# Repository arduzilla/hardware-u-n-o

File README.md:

# hardware-u-n-o

Arduino Uno format board

- Microconroller: STM32H750VB 
  - 416MHz Clock (Max 480)
  - Code & Data cache
  - 1MB SRAM
  - 128KB Flash + 2MB QSPI (direct execution from the QSPI)
  - plenty of peripherals
- RS485
- 6x Servo connector
- ... and much more

how to edit the schematics and the board layout:

install Eagle (free software for non commercial use)  https://www.autodesk.co.uk/products/eagle/free-download

clone (or fork) the arduzilla repo:
```
git clone https://github.com/arduzilla/hardware-u-n-o.git
```

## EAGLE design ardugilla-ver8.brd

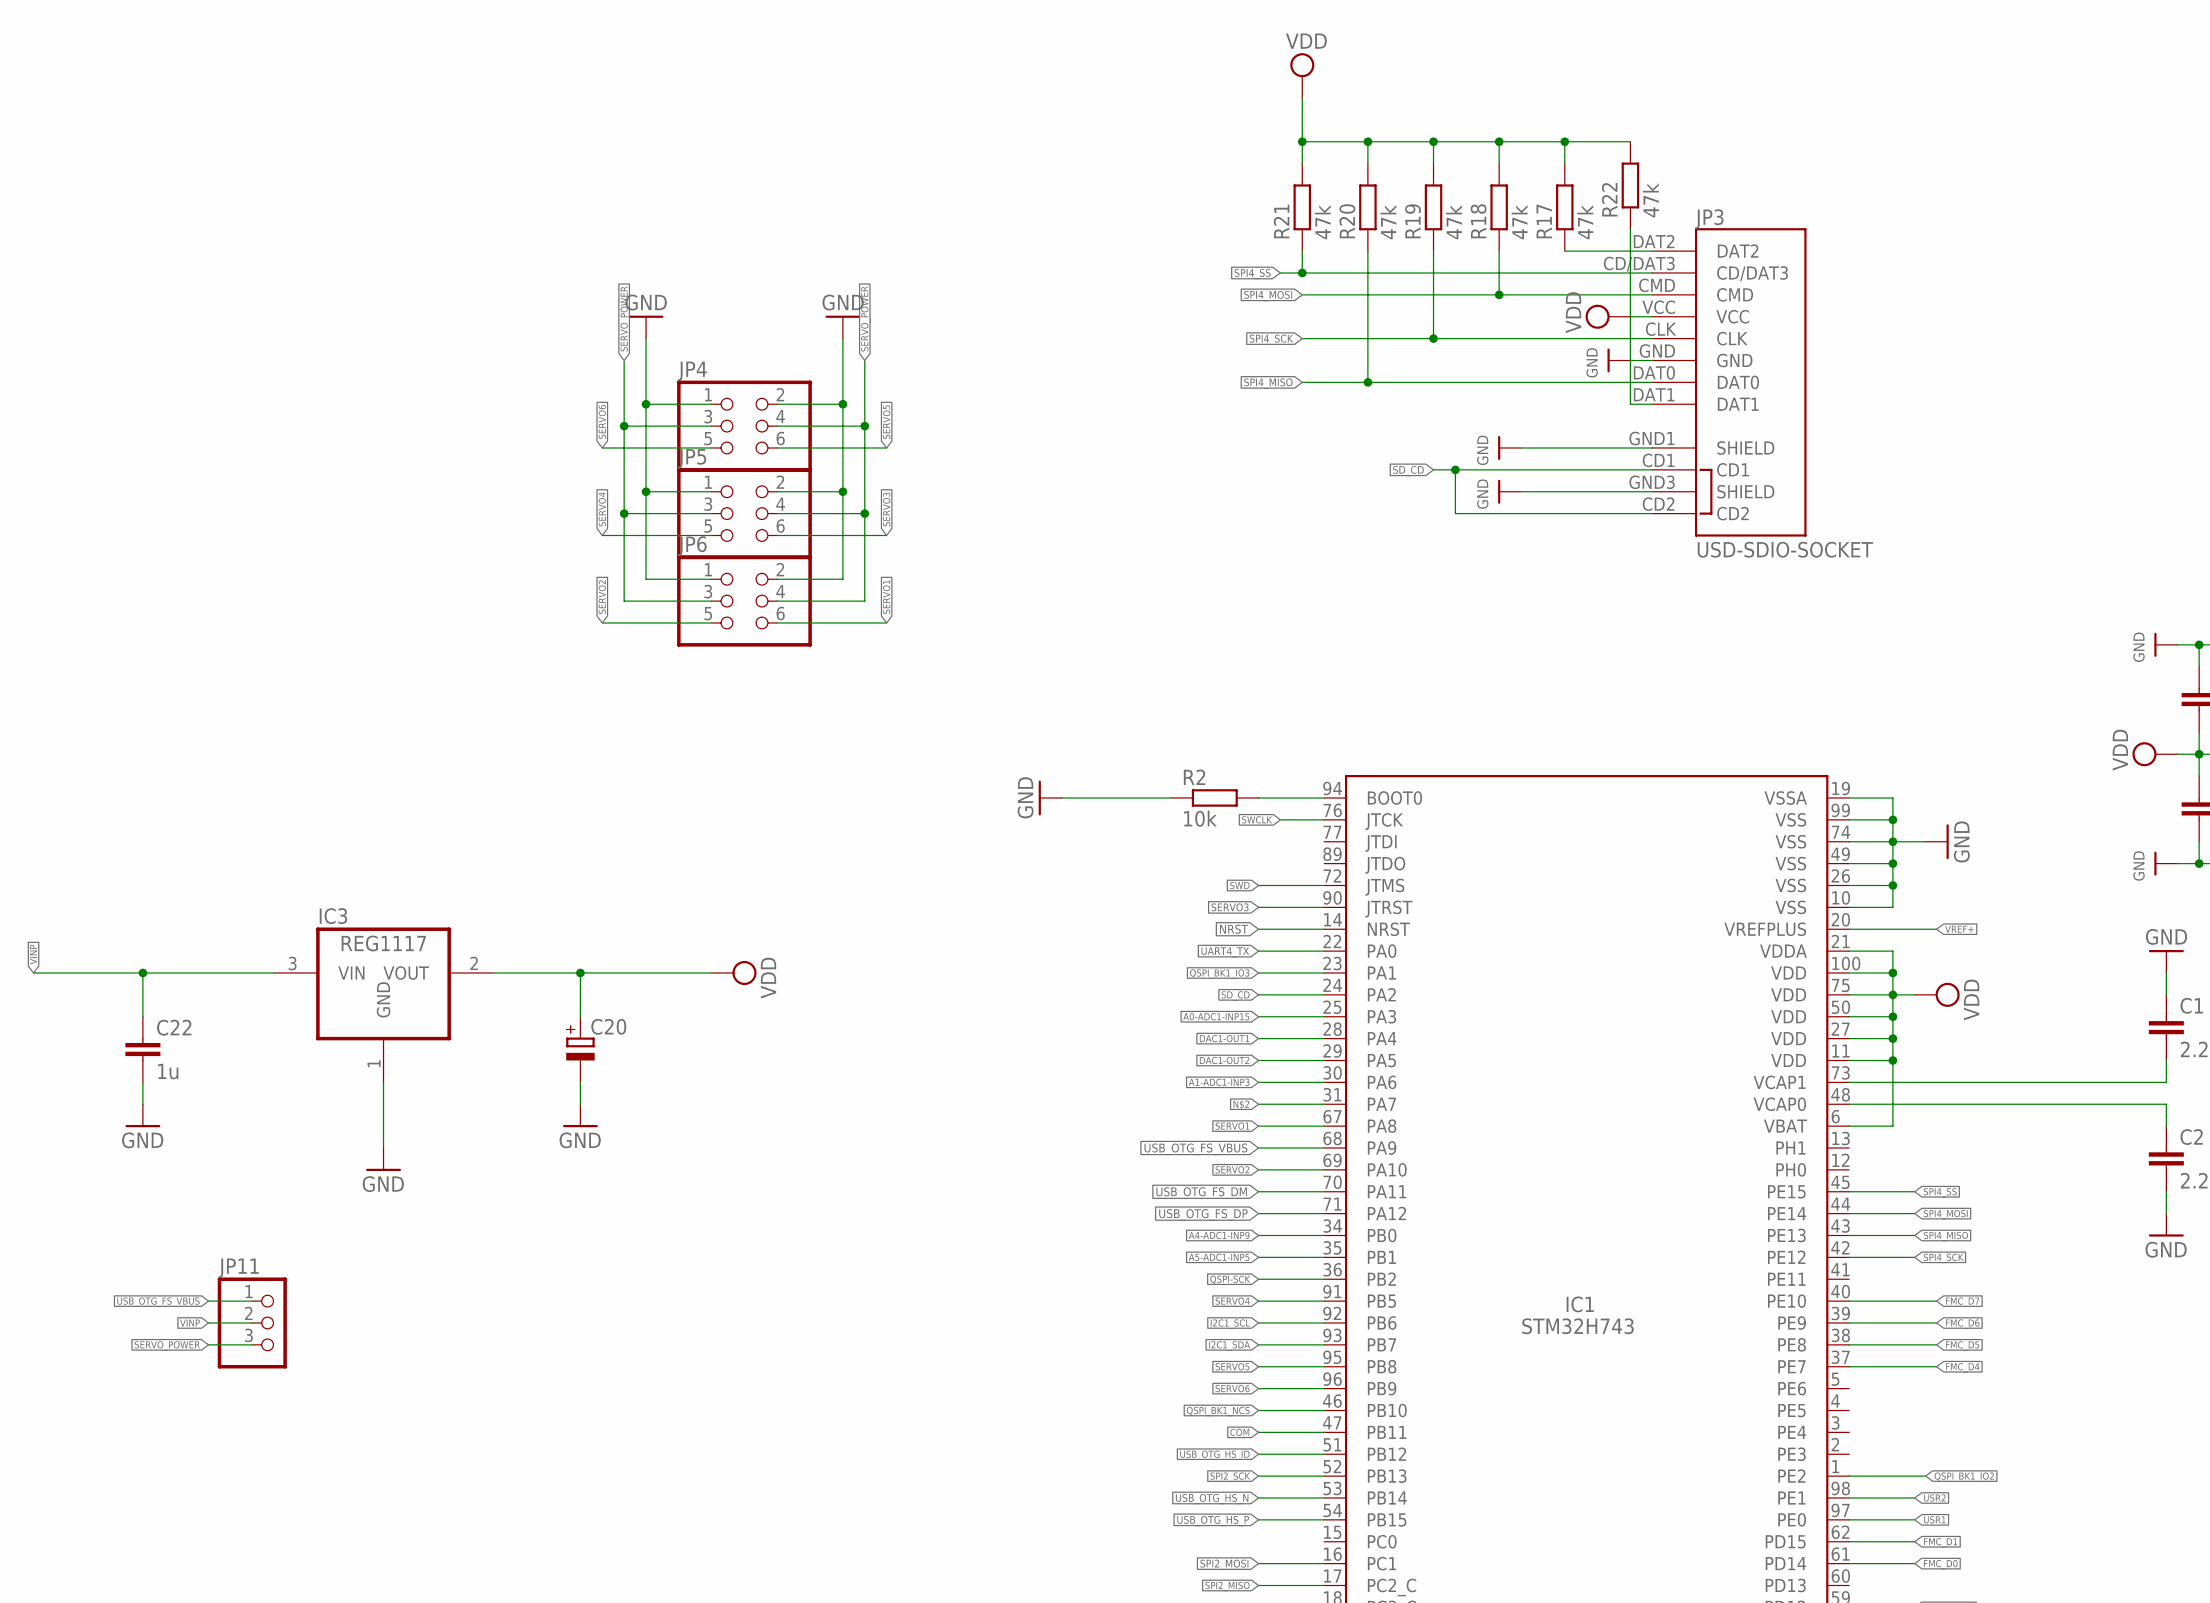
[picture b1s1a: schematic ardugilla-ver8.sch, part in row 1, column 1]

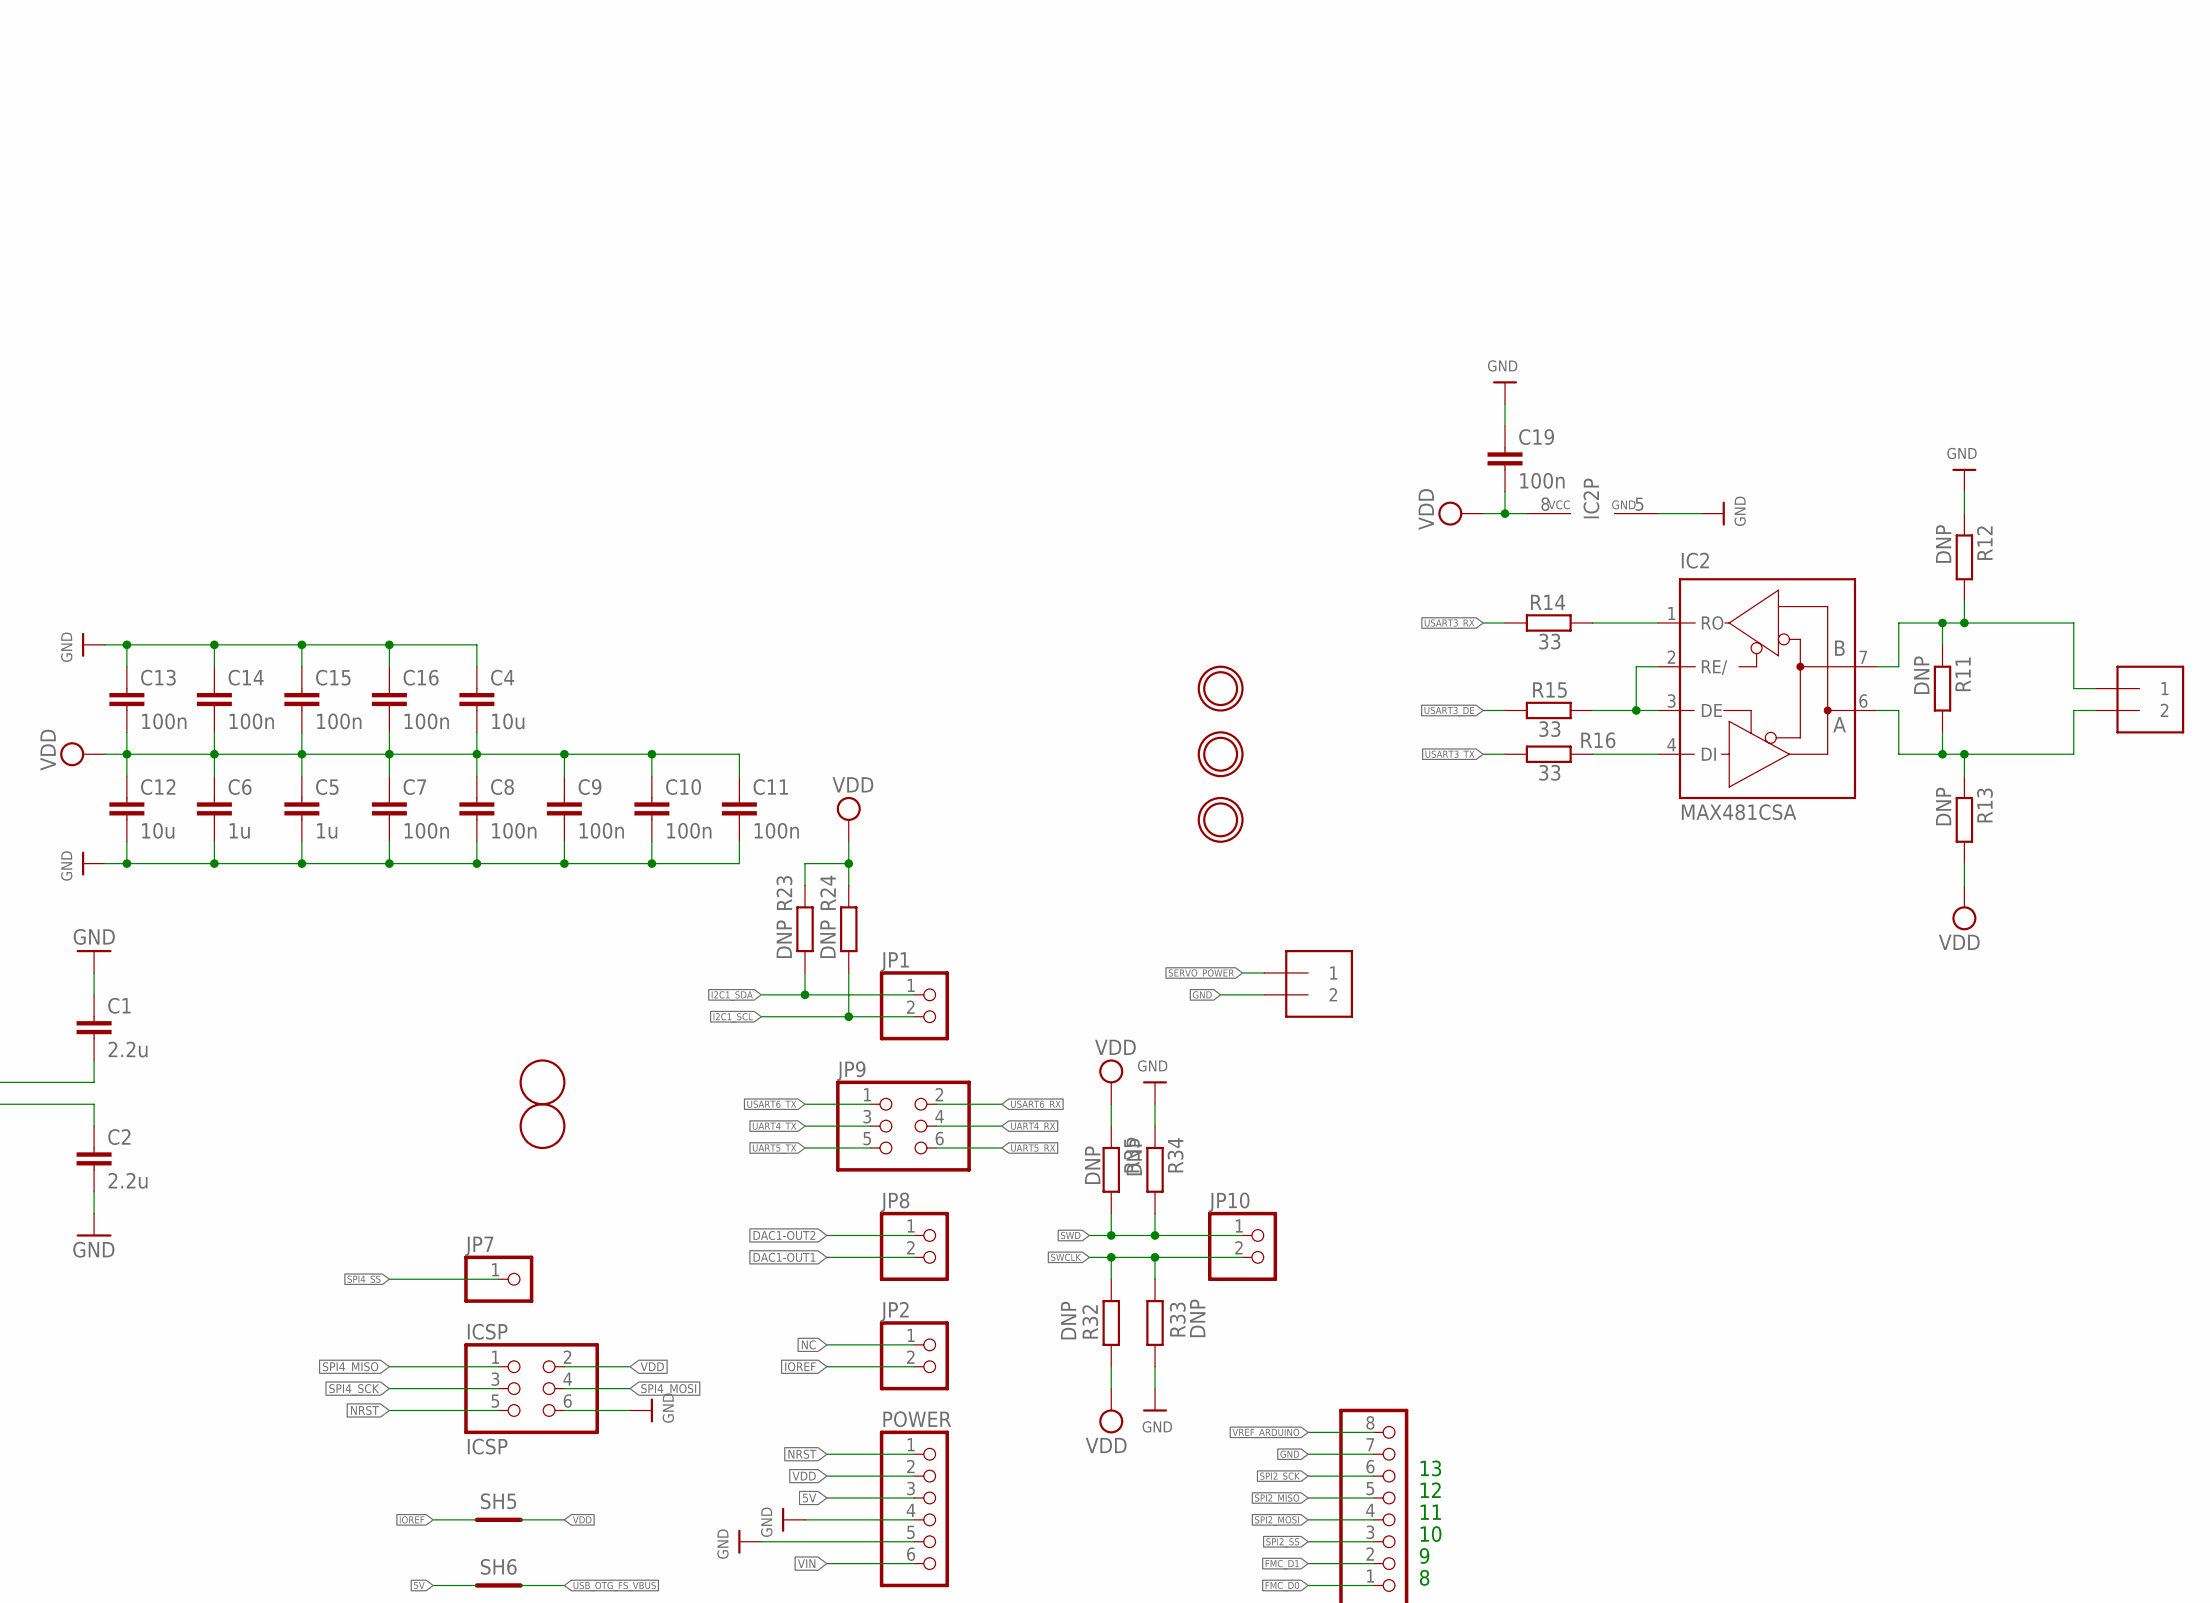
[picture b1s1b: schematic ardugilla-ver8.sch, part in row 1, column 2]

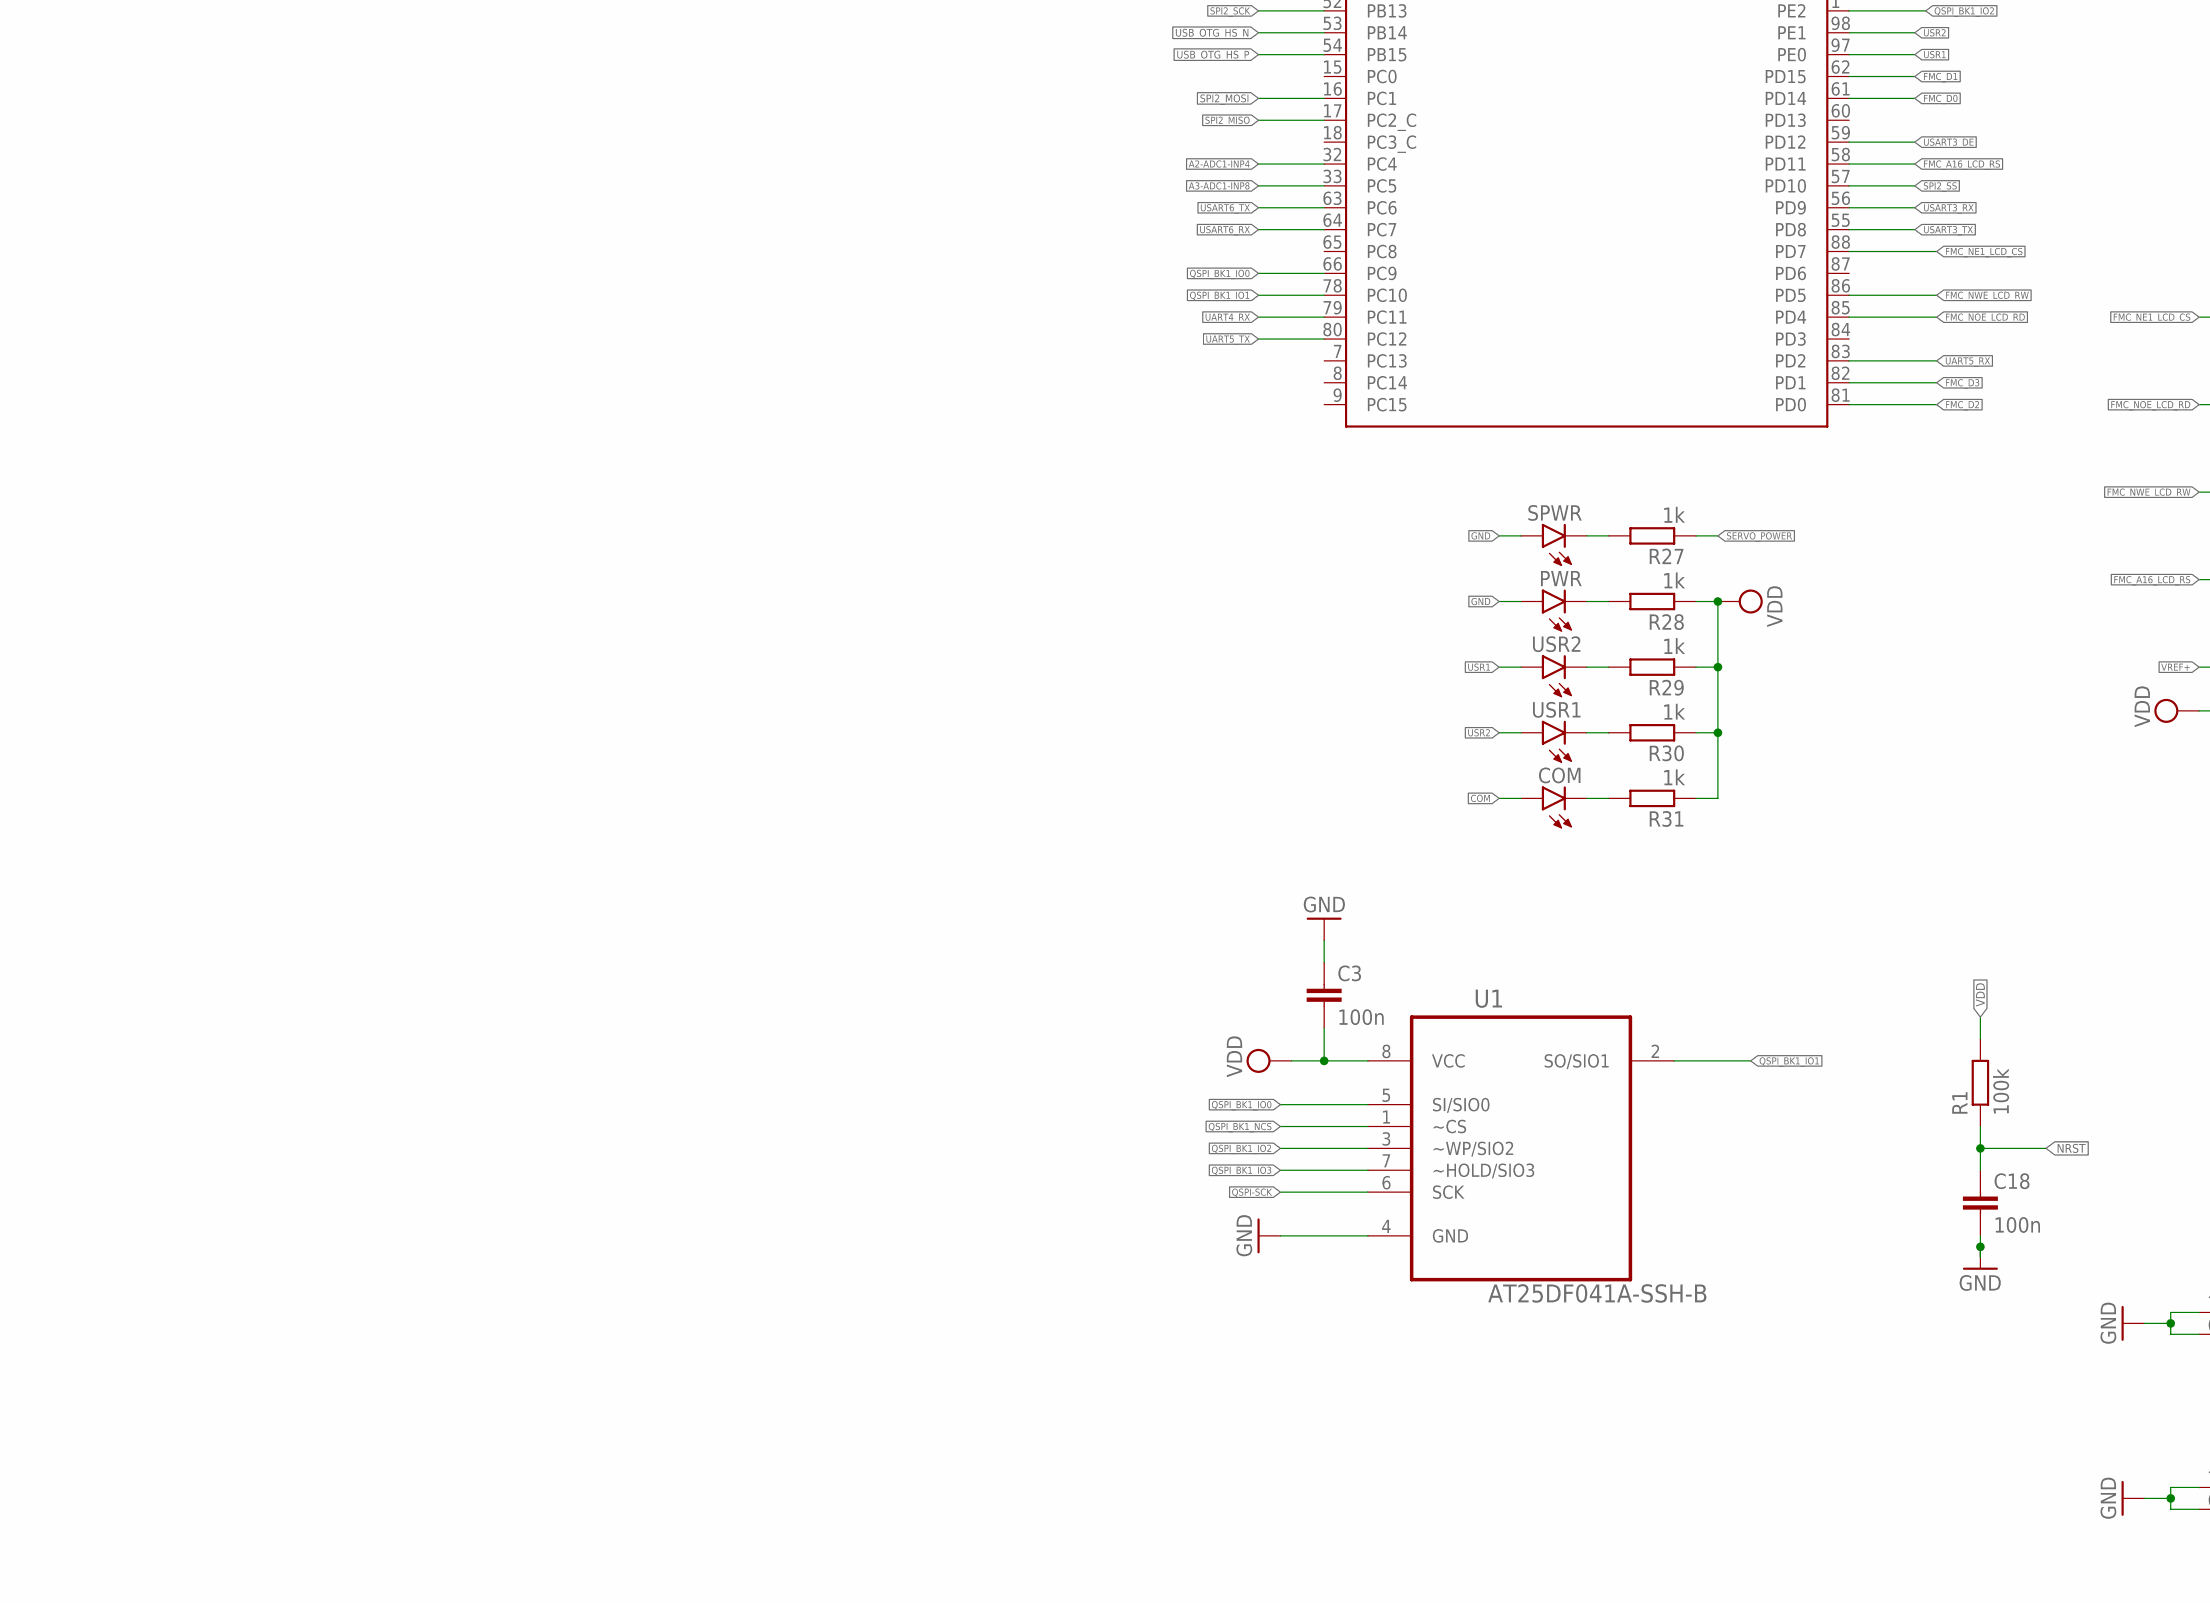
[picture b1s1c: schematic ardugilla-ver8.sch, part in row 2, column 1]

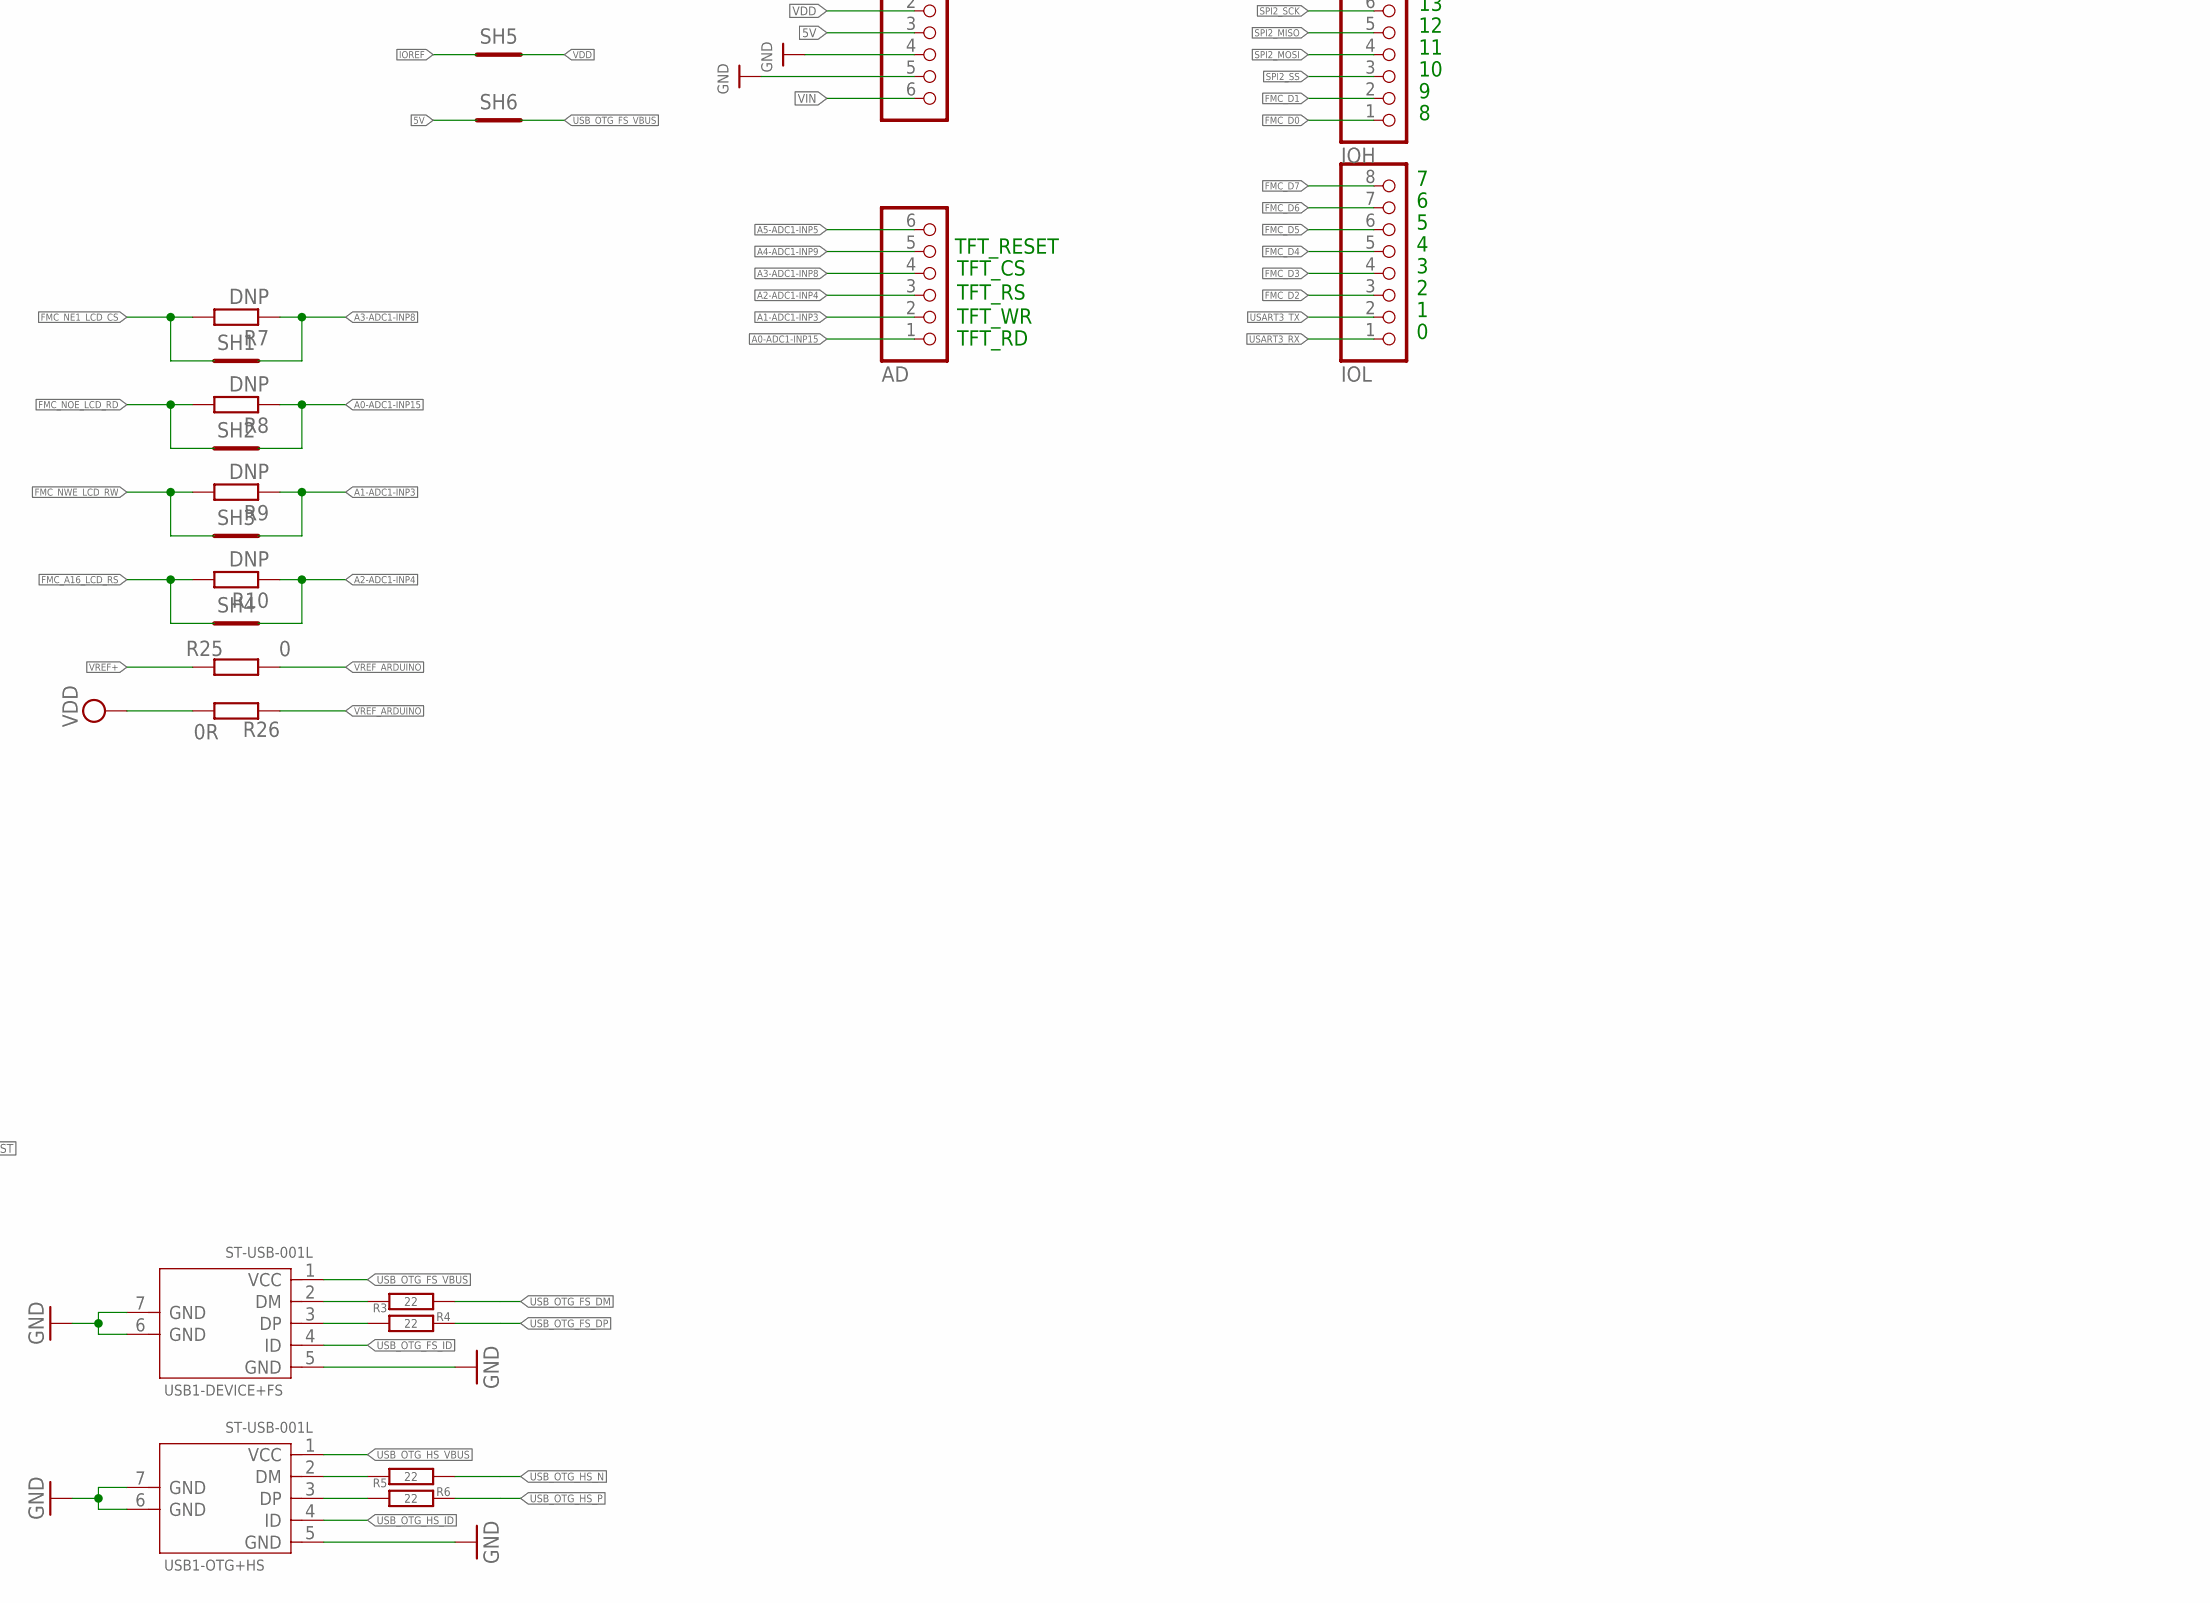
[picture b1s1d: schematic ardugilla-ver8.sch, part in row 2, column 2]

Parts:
AD: PINHD-1X6; 1X06
C1, C2: 2.2u; C0603
C3, C7, C8, C9, C10, C11, C13, C14, C15, C16, C18, C19: 100n; C0603
C4, C12: 10u; C0603
C5, C6, C22: 1u; C0603
C20: CPOL-EUE2-4; E2-4
COM: LEDSML0603; SML0603
IC1: STM32H743; LQFP100_PACKAGE
IC2: MAX481CSA; SO08
IC3: REG1117; SOT223
ICSP: ICSP; 2X03
IOH: PINHD-1X8; 1X08
IOL: PINHD-1X8; 1X08
J1, J2: 1X2-3.5MM
JP1, JP2, JP8, JP10: PINHD-1X2; 1X02
JP3: USD-SDIO-SOCKET; MICRO-SD-SOCKET-SDIO
JP4, JP5, JP6: PINHD-2X3; 2X03
JP7: PINHD-1X1CB; 1X01-CLEANBIG
JP9: PINHD-2X03_2.54-90°; 2X03/90
JP11: PINHD-1X3; 1X03
POWER: PINHD-1X6; 1X06
PWR: LEDSML0603; SML0603
R1: 100k; R0603
R2: 10k; R0603
R3, R4, R5, R6: 22; R0603
R7, R8, R9, R10: DNP; R0402
R11, R12, R13, R23, R24, R32, R33, R34, R35: DNP; R0603
R14, R15, R16: 33; R0402
R17, R18, R19, R20, R21, R22: 47k; R0603
R25: 0; R0603
R26: 0R; R0603
R27, R29, R30: 1k; R0402
R28, R31: 1k; R0603
SH1, SH2, SH3, SH4, SH5, SH6: SHORTT5; SHORT_TOP-50
SPWR: LEDSML0603; SML0603
U1: AT25DF041A-SSH-B; SOIC127P600X175-8N
U$3, U$4: FIDUCIALMOUNT; FIDUCIA-MOUNT
U$12, U$13, U$14: MICROBUILDER_MOUNTINGHOLE3.0THIN; MICROBUILDER_MOUNTINGHOLE_3.0_PLATEDTHIN
USB1-DEVICE+FS, USB1-OTG+HS: ST-USB-001L; MICRO-USB5+2P-SMD-0.65
USR1, USR2: LEDSML0603; SML0603

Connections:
5V: POWER.3, SH6.1
A0-ADC1-INP15: AD.1, IC1.25 (PA3), R8.1, SH2.2
A1-ADC1-INP3: AD.2, IC1.30 (PA6), R9.1, SH3.2
A2-ADC1-INP4: AD.3, IC1.32 (PC4), R10.1, SH4.2
A3-ADC1-INP8: AD.4, IC1.33 (PC5), R7.1, SH1.2
A4-ADC1-INP9: AD.5, IC1.34 (PB0)
A5-ADC1-INP5: AD.6, IC1.35 (PB1)
COM: COM.A, IC1.47 (PB11)
DAC1-OUT1: IC1.28 (PA4), JP8.2
DAC1-OUT2: IC1.29 (PA5), JP8.1
FMC_A16_LCD_RS: IC1.58 (PD11), R10.2, SH4.1
FMC_D0: IC1.61 (PD14), IOH.1
FMC_D1: IC1.62 (PD15), IOH.2
FMC_D2: IC1.81 (PD0), IOL.3
FMC_D3: IC1.82 (PD1), IOL.4
FMC_D4: IC1.37 (PE7), IOL.5
FMC_D5: IC1.38 (PE8), IOL.6
FMC_D6: IC1.39 (PE9), IOL.7
FMC_D7: IC1.40 (PE10), IOL.8
FMC_NE1_LCD_CS: IC1.88 (PD7), R7.2, SH1.1
FMC_NOE_LCD_RD: IC1.85 (PD4), R8.2, SH2.1
FMC_NWE_LCD_RW: IC1.86 (PD5), R9.2, SH3.1
GND: C1.1, C2.2, C3.1, C4.1, C5.2, C6.2, C7.2, C8.2, C9.2, C10.2, C11.2, C12.2, C13.1, C14.1, C15.1, C16.1, C18.2, C19.1, C20.-, C22.2, IC1.10 (VSS), IC1.19 (VSSA), IC1.26 (VSS), IC1.49 (VSS), IC1.74 (VSS), IC1.99 (VSS), IC2.5 (GND), IC3.1 (GND), ICSP.6, IOH.7, J2.2, JP3.GND, JP3.GND1 (SHIELD), JP3.GND3 (SHIELD), JP4.1, JP4.2, JP5.1, JP5.2, JP6.1, JP6.2, POWER.4, POWER.5, PWR.A, R2.1, R12.1, R33.2, R34.1, SPWR.A, U1.4 (GND), USB1-DEVICE+FS.5 (GND), USB1-DEVICE+FS.6 (GND), USB1-DEVICE+FS.7 (GND), USB1-OTG+HS.5 (GND), USB1-OTG+HS.6 (GND), USB1-OTG+HS.7 (GND)
I2C1_SCL: IC1.92 (PB6), JP1.2, R24.1
I2C1_SDA: IC1.93 (PB7), JP1.1, R23.1
IOREF: JP2.2, SH5.1
unnamed: IC1.94 (BOOT0), R2.2
unnamed: C1.2, IC1.73 (VCAP1)
unnamed: C2.1, IC1.48 (VCAP0)
unnamed: R27.2, SPWR.C
unnamed: R3.2, USB1-DEVICE+FS.2 (DM)
unnamed: PWR.C, R28.2
unnamed: R4.2, USB1-DEVICE+FS.3 (DP)
unnamed: R5.2, USB1-OTG+HS.2 (DM)
unnamed: R6.2, USB1-OTG+HS.3 (DP)
unnamed: R29.2, USR2.C
unnamed: R30.2, USR1.C
unnamed: COM.C, R31.2
unnamed: IC2.2 (RE/), IC2.3 (DE), R15.2
unnamed: IC2.4 (DI), R16.2
unnamed: IC2.1 (RO), R14.2
unnamed: IC2.7 (B), J1.1, R11.1, R12.2
unnamed: IC2.6 (A), J1.2, R11.2, R13.1
NC: JP2.1
NRST: C18.1, IC1.14 (NRST), ICSP.5, POWER.1, R1.1
QSPI-SCK: IC1.36 (PB2), U1.6 (SCK)
QSPI_BK1_IO0: IC1.66 (PC9), U1.5 (SI/SIO0)
QSPI_BK1_IO1: IC1.78 (PC10), U1.2 (SO/SIO1)
QSPI_BK1_IO2: IC1.1 (PE2), U1.3 (~WP/SIO2)
QSPI_BK1_IO3: IC1.23 (PA1), U1.7 (~HOLD/SIO3)
QSPI_BK1_NCS: IC1.46 (PB10), U1.1 (~CS)
SD_CD: IC1.24 (PA2), JP3.CD1, JP3.CD2
SD_DAT1: JP3.DAT1, R22.1
SD_DAT2: JP3.DAT2, R17.1
SERVO1: IC1.67 (PA8), JP6.6
SERVO2: IC1.69 (PA10), JP6.5
SERVO3: IC1.90 (JTRST), JP5.6
SERVO4: IC1.91 (PB5), JP5.5
SERVO5: IC1.95 (PB8), JP4.6
SERVO6: IC1.96 (PB9), JP4.5
SERVO_POWER: J2.1, JP4.3, JP4.4, JP5.3, JP5.4, JP6.3, JP6.4, JP11.3, R27.1
SPI2_MISO: IC1.17 (PC2_C), IOH.5
SPI2_MOSI: IC1.16 (PC1), IOH.4
SPI2_SCK: IC1.52 (PB13), IOH.6
SPI2_SS: IC1.57 (PD10), IOH.3
SPI4_MISO: IC1.43 (PE13), ICSP.1, JP3.DAT0, R20.1
SPI4_MOSI: IC1.44 (PE14), ICSP.4, JP3.CMD, R18.1
SPI4_SCK: IC1.42 (PE12), ICSP.3, JP3.CLK, R19.1
SPI4_SS: IC1.45 (PE15), JP3.CD/DAT3, JP7.1, R21.1
SWCLK: IC1.76 (JTCK), JP10.2, R32.1, R33.1
SWD: IC1.72 (JTMS), JP10.1, R34.2, R35.2
UART4_RX: IC1.79 (PC11), JP9.4
UART4_TX: IC1.22 (PA0), JP9.3
UART5_RX: IC1.83 (PD2), JP9.6
UART5_TX: IC1.80 (PC12), JP9.5
USART3_DE: IC1.59 (PD12), R15.1
USART3_RX: IC1.56 (PD9), IOL.1, R14.1
USART3_TX: IC1.55 (PD8), IOL.2, R16.1
USART6_RX: IC1.64 (PC7), JP9.2
USART6_TX: IC1.63 (PC6), JP9.1
USB_OTG_FS_DM: IC1.70 (PA11), R3.1
USB_OTG_FS_DP: IC1.71 (PA12), R4.1
USB_OTG_FS_ID: USB1-DEVICE+FS.4 (ID)
USB_OTG_FS_VBUS: IC1.68 (PA9), JP11.1, SH6.2, USB1-DEVICE+FS.1 (VCC)
USB_OTG_HS_ID: IC1.51 (PB12), USB1-OTG+HS.4 (ID)
USB_OTG_HS_N: IC1.53 (PB14), R5.1
USB_OTG_HS_P: IC1.54 (PB15), R6.1
USB_OTG_HS_VBUS: USB1-OTG+HS.1 (VCC)
USR1: IC1.97 (PE0), USR2.A
USR2: IC1.98 (PE1), USR1.A
VDD: C3.2, C4.2, C5.1, C6.1, C7.1, C8.1, C9.1, C10.1, C11.1, C12.1, C13.2, C14.2, C15.2, C16.2, C19.2, C20.+, IC1.6 (VBAT), IC1.11 (VDD), IC1.21 (VDDA), IC1.27 (VDD), IC1.50 (VDD), IC1.75 (VDD), IC1.100 (VDD), IC2.8 (VCC), IC3.2 (VOUT), ICSP.2, JP3.VCC, POWER.2, R1.2, R13.2, R17.2, R18.2, R19.2, R20.2, R21.2, R22.2, R23.2, R24.2, R26.2, R28.1, R29.1, R30.1, R31.1, R32.2, R35.1, SH5.2, U1.8 (VCC)
VIN: POWER.6
VINP: C22.1, IC3.3 (VIN), JP11.2
VREF+: IC1.20 (VREFPLUS), R25.2
VREF_ARDUINO: IOH.8, R25.1, R26.1

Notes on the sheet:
TFT_RESET
TFT_CS
TFT_RS
TFT_WR
TFT_RD

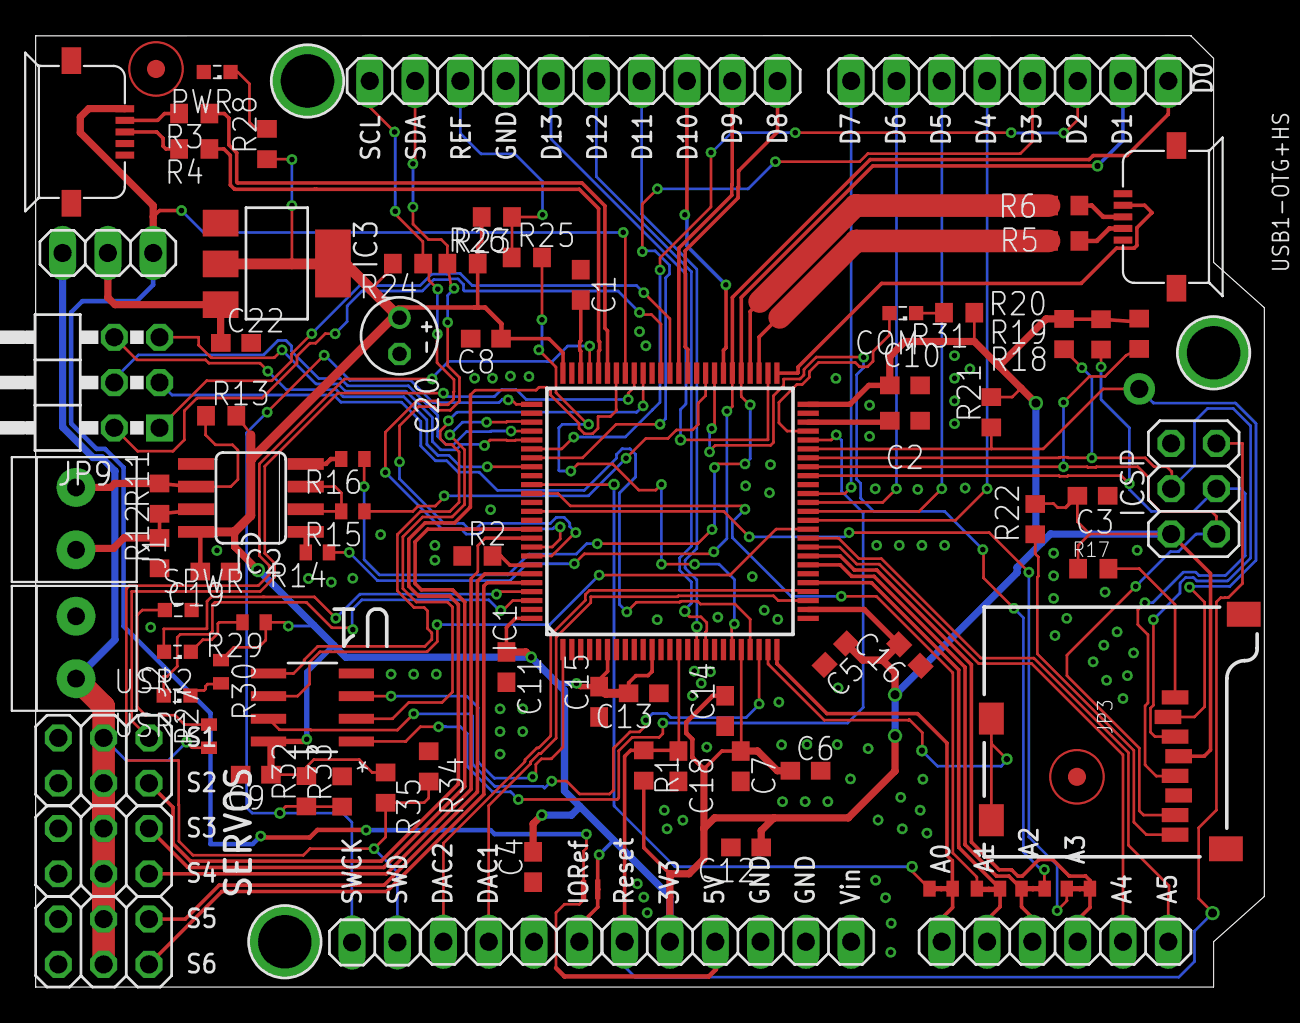
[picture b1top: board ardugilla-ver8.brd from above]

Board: 2 copper layers, 68.9 x 53.3 mm, 95 parts (0 on the bottom side), 91 nets.

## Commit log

2019-11-04 Initial commit
    Upload of the initial scectes of the board. Not a decent schematics .

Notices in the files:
parts and their libraries:
SparkFun-Connectors: Licensing: Creative Commons ShareAlike 4.0 International - https://creativecommons.org/licenses/by-sa/4.0
NXP_60_26022015: This library may be distributed and adapted freely for any purpose, as long as NXP is credited and any new creation is licensed under the same terms.
